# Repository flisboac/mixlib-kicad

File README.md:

# mixlib-kicad

Assorted symbols and footprints for the ones not afraid to use fancy stuff.

... But in fact, this is just my personal KiCAD component library.

## Credits:

- marbastlib (awesome library, do ckeck it out!)
- keebio
- Mouser, Digikey, etc.
- Everyone uploading stuff to SnapEDA, etc.
- Probably a lot more, for stuff I don't know the origin anymore. (In that case, please let me know!)

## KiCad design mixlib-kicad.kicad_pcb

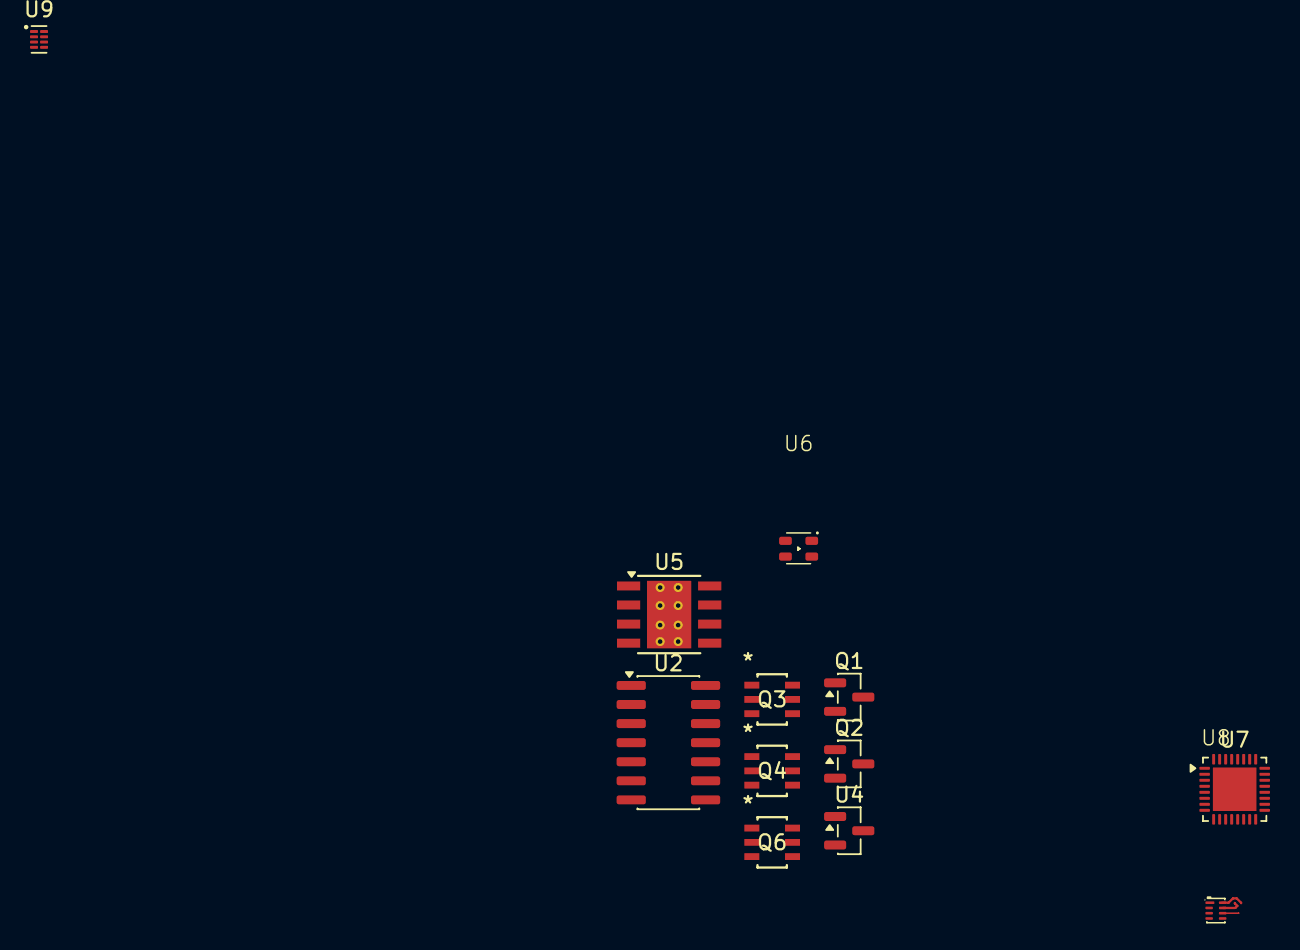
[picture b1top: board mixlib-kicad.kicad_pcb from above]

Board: 2 copper layers, 12 parts (0 on the bottom side), 7 nets.

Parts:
Q1, Q2: MMBT5551L; SOT-23
Q3: PMD3001D; SC-74_SOT-457_NEX
Q4: PBSS4160DS; SC-74_SOT-457_NEX
Q6: PBSS4160DPN; SC-74_SOT-457_NEX
U2: MCP6404; SOIC-14_3.9x8.7mm_P1.27mm
U4: LM4040DBZ-10; SOT-23
U5: TPS5430DDA; TI_SO-PowerPAD-8_ThermalVias
U6: TJ-S1615CY6TGLCCYRGY-A5; LED-3_RGB-0603_1615Metric
U7: CH32V006K8U6; QFN-32-1EP_4x4mm_P0.4mm_EP2.9x2.9mm
U8: TXS0102DQE; vendor-ti-DQE0008A
U9: TXS0102DQE; X2SON-8_1.4x1mm_P0.35mm

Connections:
/VCC: U2.4 (V+), U5.5 (EN), U5.7 (VIN)
/VDRIVER_BASE: Q3.1 (B), Q6.1 (C1)
/VDRIVER_SW: Q6.2 (B1), Q6.3 (C2)
/VDRIVER_VCC: Q3.5 (C1_1), Q3.6 (C1_2)
/VDRIVER_VSS: Q3.2 (C2_1), Q3.3 (C2_2)
/VOUT: Q1.3 (C), Q2.3 (C)
GND: Q1.2 (E), Q2.2 (E), Q4.3 (C2), Q4.4 (E2), Q4.5 (B2), Q6.5 (B2), U2.11 (V-), U4.2 (A), U5.6 (GND), U5.9 (GNDPAD)

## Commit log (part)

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2023-03-31 feat: initial commit
2025-04-15 feat: add various breakout boards
2025-04-15 feat(pmic/battery): add BQ25672RQMR
2025-04-17 refactor(pmic/battery): bq25672: update symbol
2025-04-17 feat(ic/usb): add HUSB238
2025-04-18 feat(connector/jumper): add 4-way solder jumper
2025-04-18 refactor(connector/jumper): make 4-way solder jumper smaller
2025-04-18 refactor(connector/jumper): adjust 4-way solder jumper smaller symbol shape
2025-04-18 feat(pmic/vreg): add TPS7A2601
2025-04-20 feat(discrete/mosfet): add BSS138PS
2025-04-20 feat(discrete/mosfet): add Si7223DN and Si7224DN
2025-04-20 refactor: reconfigure pins of BQ25672 and TPSA2601
2025-04-21 feat(pmic/battery): add MAX172x5G, MAX17055ETB
2025-04-21 refactor(pmic/battery): MAX172x5G, MAX17055ETB: reduce symbol size
2025-04-21 refactor(pmic/battery): MAX172x5G: reorder CELL pins
2025-04-22 feat(pmic/vreg): add TPS63070
2025-04-22 fix(pmic/vreg): TPS63070: set proper default footprint and adjust footprint filters
2025-04-25 fix(pmic/battery): MAX172x5G: adjust footprint to the correct size
2025-04-27 feat(discrete/mosfet): add DMC3025LDV
2025-04-27 fix(discrete/mosfet): DMC3025LDV: adjust number of pins
2025-05-02 feat: add spice models folder
2025-05-02 fix(spice/discrete/zener): fix spice script syntax
2025-05-02 fix(spice): fix model file syntax
2025-05-04 feat(mosfet): add DMT6005LPS, STL130N6F7
2025-05-04 refactor(mosfet): redefine path for 3d models in terms of user-provided path MIXLIB_KICAD_3DMODELS_DIR
2025-05-06 feat(discrete/mosfet): footprints: make it easier to connect heatpads to their respective pins
2025-05-12 feat(spice): add op-amp: ADA4522
2025-05-18 feat: various improvements, components and simulation scripts
2025-05-18 feat: add common schottky diodes
2025-05-18 feat: add various MOSFETs
2025-05-18 fix: simplify some MOSFET footprints and add missing simulation scripts
2025-05-18 chore: saving project state
2025-05-18 add: copy ADA4522 from KiCad and assign default simulation scripts
2025-05-18 feat: add BZT52 series symbol with fixed simulation symbols
2025-05-18 fix: various fixes
2025-05-24 feat: add some bjt transistors and fix simulation scripts
2025-05-25 feat(discrete/npn): PMD3001D: redesign symbol
2025-05-25 feat: add npn/pnp and zener parts
2025-10-11 refactor(discrete-mosfet): Si4599: remodel as two distinct MOSFET symbols
2025-10-11 refactor(discrete-mosfet): Si4599: move to the proper symbol library and add SPICE models
2025-10-11 refactor(discrete-mosfet): Si4599: center symbol
2025-10-11 refactor(misc-board): sparkfin_max17048: add footprint and reassign pins
2025-10-11 feat(discrete-mosfet): add FS8205A 8-pin
2025-10-12 feat(pmic-board): add generic TP4056 charger board with DW01 Battery protection
2025-10-12 fix: remove unwanted submodules
2025-10-12 fix(pmic-board): TP4056_DW01_Charger: assign the default footprint
2025-10-12 feat(pmic-supervisor): add RT9829
2025-10-12 feat(pmic-supervisor): add TPS380x
2025-10-12 feat(pmic-switch): add LM66200
2025-10-13 feat(ic-esd): add SMFxxCT1G
2025-10-13 refactor(symbols/ic-esd): SMFxxCT1G: reposition labels to a sane location
2025-10-13 feat(pmic-vreg): add AP7361C-xxY5
2025-10-14 refactor(pmid/battery): BQ24295: reorganize pins
2025-10-15 refactor(ic/mcu): add CH32X035F7P6
2025-10-16 feat(ic-mcu): add CH32V006K8U6
2025-10-17 feat(discrete/led): add SK6805-EC14
2025-10-18 fix: correct minor mistakes in footprints and 3d models
2025-10-20 feat: add cheap environment sensor boards' symbols and footprints
2025-10-20 feat(pmic-board): XL63070: add footprint
2025-10-20 feat(discrete-board): add SparkFun Logic Level Converter V2
2025-10-20 fix(discrete-board): Sparkfun_LogicLevelConverter_V2: reorder pins and add footprint
2025-10-20 feat(soc-board): add ESP32-S3-Pico
2025-10-22 feat(discrete/board): add XL0401 Ideal diode board
2025-10-22 fix(discrete/board): XL0401_IdealDiode: fix footprint pinout
2025-10-22 refactor(discrete/board): Sparkfun_LogicLevelConverter_V2: resize symbol to be smaller
2025-10-28 feat(misc/board): add Generic_TXS0108_Board
2026-01-18 chore: change all .cir files to LF (Unix) line endings
2026-01-28 feat(pmic-battery): add AXP2585
2026-02-12 feat: add a bunch of new components
2026-02-12 feat(mixlib-discrete-led): reduce ARGB components' footprints
2026-02-14 feat: add first-pin indicator on footprints lacking such
2026-02-16 feat(discrete-mosfet): add SiA931DJ
2026-02-16 refactor: small adjustment on AXP2585 symbol's pins
2026-02-16 feat(electromechanic-switch): add MSK-12C01
2026-02-16 refactor(pmic-switch): TPS2116, TPS2117: improve symbol pin spacing
2026-02-16 feat(electromechanic-switch): add TS-A002
2026-02-16 feat(pmic-vreg): add TPS63802
2026-02-16 feat(electromechanic-switch): fix MSK-12C01 footprint association
2026-02-18 feat: add small form-factor MOSFETs
2026-02-18 feat(discrete-mosfet): add Si1539CDL
2026-02-20 feat: add many small form-factor MOSFETs
2026-02-23 refactor(electromechanic-switch): TS-A002: add 3D model
2026-03-09 feat(discrete-mosfet): add DMN3032LFDBQ
2026-03-09 feat(pmic-vreg): add RT9080
2026-03-09 fix(pmic-vreg): RT9080: fix symbol pinouts
2026-03-09 fix(discrete-mosfet): si3993CDV: fix symbol pinouts
2026-03-15 fix: properly configure location of 3D models
2026-03-15 feat(soc-stm32g0): add STM32G071G8Ux (28-pin) and variants
2026-03-15 fix: put some footprints in the correct folders
2026-03-15 feat(ic-usb): add TPS6S300A and TPS8S300A
2026-03-15 feat(ic-usb): TPS6S300A, TPS8S300A: fix pinouts
2026-03-15 fix(pmic-battery): minor adjustments to MAX17055 footprint
2026-03-16 fix(pmic-battery): bq25672: minor adjustments to the footprint
2026-03-17 feat: add many mosfets
2026-03-26 feat(pmic-battery_: add BQ25620
2026-03-26 fix(pmic-battery): BQ25620: set correct 3D model path
2026-03-27 feat(pmic-switch): add TPS2121
2026-03-28 refactor(pmic-switch): TPS2121: reposition CP2 pin in symbol
2026-03-28 refactor(pmic-switch): TPS2121: reposition symbol pins
2026-03-29 feat(pmic-vreg): add adjustable NCP718
2026-03-29 feat(discrete-led): add generic Aliexpress 0603 discrete LED
2026-03-29 refactor(discrete-led): rearrange generic Aliexpress 0603 discrete LED symbol
2026-05-02 feat(discrete-mosfet): add DMN31D5UDJ
2026-05-04 feat(pmic-battery): add BQ25628 and BQ25629
2026-06-07 feat(ic-mcu): add CH32V/CH32F MCUs
2026-06-07 feat(pmic-switch): add CH213K and CH217K
2026-06-07 feat(interface-uart): add THVD1400
2026-06-26 feat(ic-logic): add TXS0102DQE
